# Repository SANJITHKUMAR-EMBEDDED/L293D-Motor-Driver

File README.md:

# L293D-Motor-Driver
# Project #3: L293D Motor Driver Module

This is Project 3 of my #50BoardChallenge. This is a 2-channel H-Bridge motor driver board, designed to control the speed and direction of two DC motors.

This project was a major step up in complexity, focusing on **power management** and **heatsinking**.

## Features
* Drives two DC motors with full forward, reverse, and speed control.
* Based on the L293D H-Bridge IC.
* Dual power inputs: a `+V` (Motor) supply and a `VCC` (Logic) supply.
* On-board jumpers to enable "Always On" mode or allow for PWM speed control.
* Screw terminals for all high-current connections (power and motor outputs).

## Professional Design Rules
This board was designed to handle high currents and manage heat:

* **Heatsinking:** Used a **top-layer copper pour** connected directly to the L293D's 4 central `GND` pins to act as a heatsink and pull heat away from the chip.
* **Net Classes:** Set up three distinct Net Classes:
    * **`MOTOR_POWER` (60 mil):** For all high-current motor and `+V` traces.
    * **`LOGIC_POWER` (20 mil):** For the `VCC` and logic `GND` traces.
    * **`Default` (8 mil):** For all low-current logic signals (`IN1-4`, `EN1-2`).
* **Solid `GND` Plane:** Used a solid copper pour on the **bottom layer** for a stable, low-noise ground reference.
* **DRC:** The final design passed all Design Rules Checks with **0 errors and 0 warnings**.

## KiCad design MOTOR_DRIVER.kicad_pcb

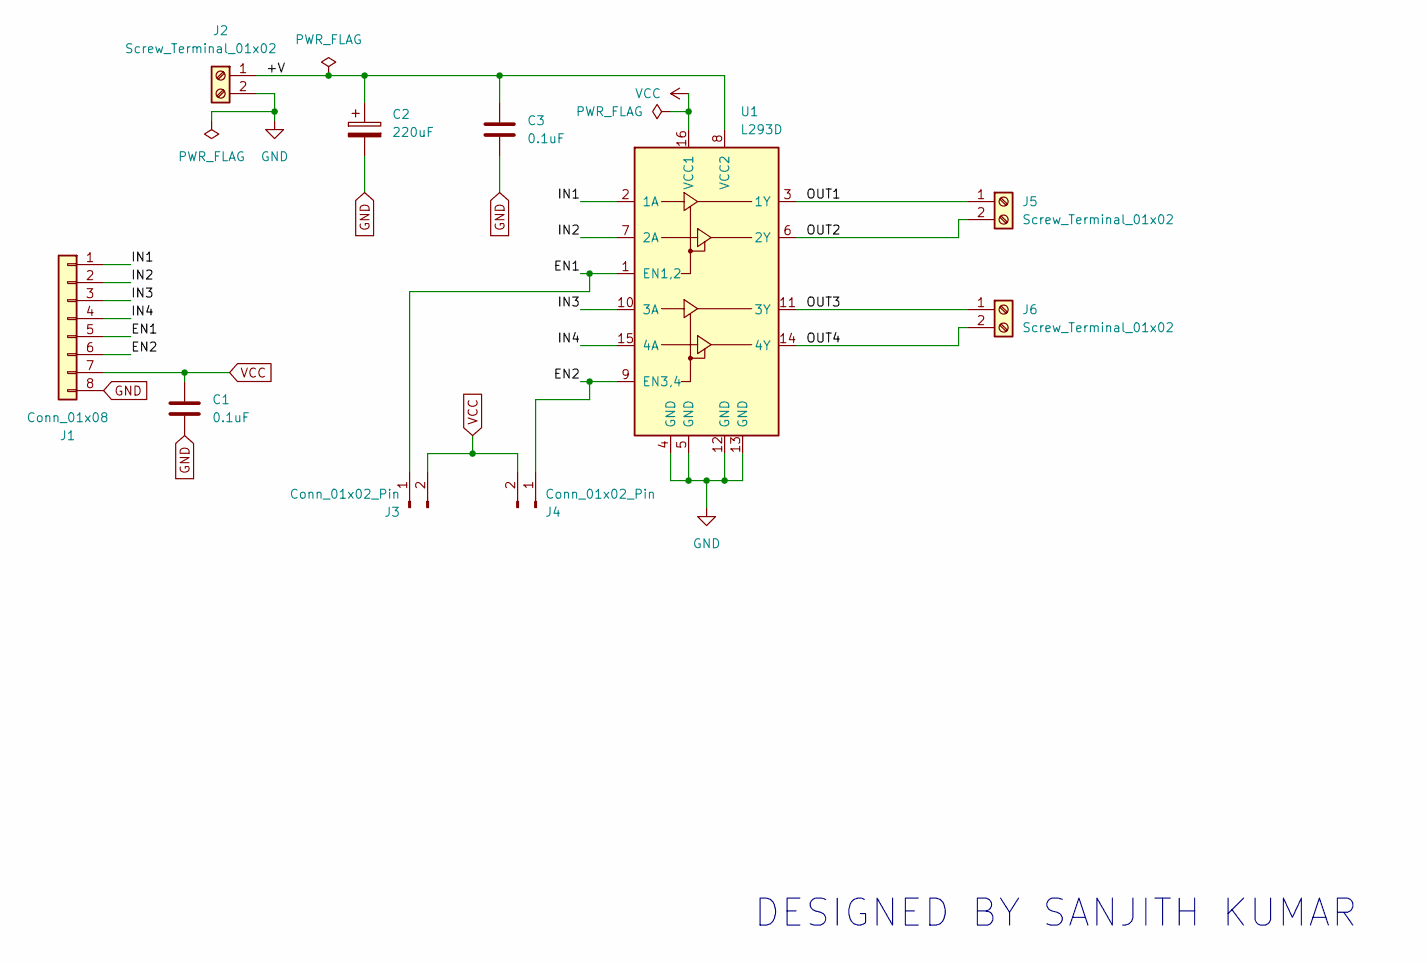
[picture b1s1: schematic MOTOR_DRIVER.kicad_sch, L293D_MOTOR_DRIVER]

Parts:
C1, C3: 0.1uF; C_Disc_D4.7mm_W2.5mm_P5.00mm
C2: 220uF; CP_Radial_D6.3mm_P2.50mm
J1: Conn_01x08; PinHeader_1x08_P2.54mm_Vertical
J2, J5, J6: Screw_Terminal_01x02; PHOENIX_1729128
J3, J4: Conn_01x02_Pin; PinHeader_1x02_P2.54mm_Vertical
U1: L293D; DIP-16_W7.62mm

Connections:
/+V: C2.1, C3.1, J2.1, U1.8 (VCC2)
/EN1: J1.5, J3.1, U1.1 (EN1,2)
/EN2: J1.6, J4.1, U1.9 (EN3,4)
/IN1: J1.1, U1.2 (1A)
/IN2: J1.2, U1.7 (2A)
/IN3: J1.3, U1.10 (3A)
/IN4: J1.4, U1.15 (4A)
/OUT1: J5.1, U1.3 (1Y)
/OUT2: J5.2, U1.6 (2Y)
/OUT3: J6.1, U1.11 (3Y)
/OUT4: J6.2, U1.14 (4Y)
GND: C1.2, C2.2, C3.2, J1.8, J2.2, U1.4 (GND), U1.5 (GND), U1.12 (GND), U1.13 (GND)
VCC: C1.1, J1.7, J3.2, J4.2, U1.16 (VCC1)

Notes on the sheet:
DESIGNED BY SANJITH KUMAR

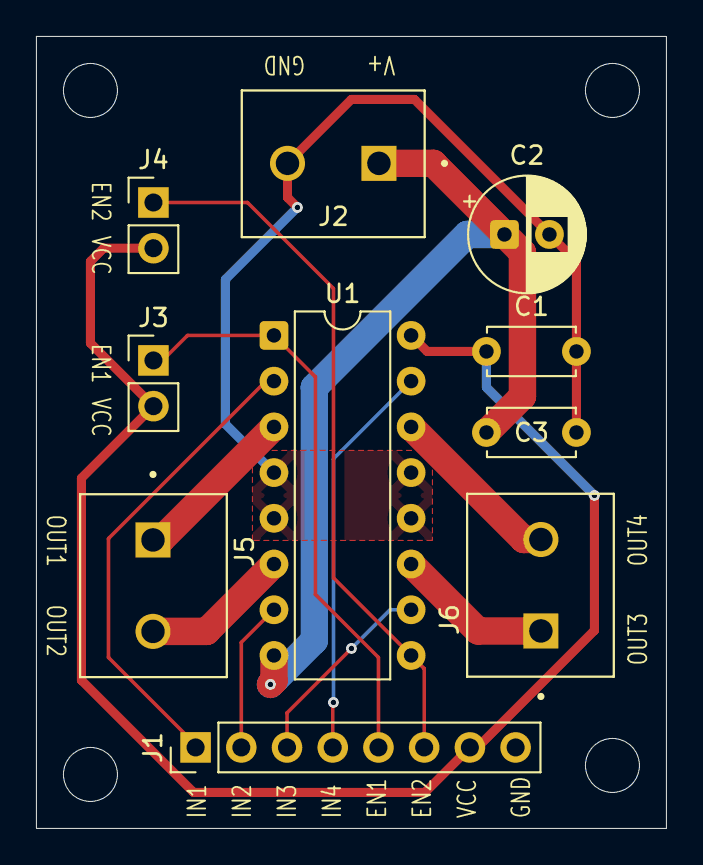
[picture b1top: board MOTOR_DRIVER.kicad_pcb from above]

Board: 2 copper layers, 35.0 x 44.0 mm, 10 parts (0 on the bottom side), 13 nets.

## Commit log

2025-11-09 Remove image source from README
    Removed image source from README.md.
2025-11-09 Remove image placeholder from README
    Removed image placeholder from README.
